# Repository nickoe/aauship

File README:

AAUSHIP
=======
An Autonomous Unmanned Vessel platform

Git repository
--------------
We now have a common git repository we han push to. You can clone it like this
on unix. If you are not familiar with git, I reccomend that you read through
http://gitref.org/, use it as a reference and try to do all of it just to get
familiar with git.

	git clone /afs/ies.auc.dk/www/www.auv.aau.dk/repo/aauship.git

You now have a folder called aauship in the folder you cloned it in.

As you see the repository is directly on AFS, so you have to be authenticated to
 be able to pull and push.

Other stuff that is good to know
https://sites.google.com/site/tjinguytech/charging-how-tos/lipo-terminology

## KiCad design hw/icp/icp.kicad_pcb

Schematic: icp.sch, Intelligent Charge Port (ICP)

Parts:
BZ1: KX1205
C1, C2, C3, C4, C5, C6, C7, C8: 100n
D1: Alarm
D2: ON
D3: Sample
D4: Data
D5: AUX
K1: Tacho0
K2: Tacho1
P1, P2: PX0707/06S
P3, P4: Deans Male
P5, P6: JST-XH
P7: WLD1
P8: I²C
P9: 5V PWR
P10: UART
P11: WLD2
Q1, Q2, Q3, Q4: BC846
R1, R3: 7K5
R2, R4: 2K7
R5, R8, R11, R14, R17, R20: 9K1
R6, R9: 91R
R7, R10: 1K3
R12, R15: 330R
R13, R16: 910R
R18, R21: 560R
R19, R22: 680R
R23, R24, R25, R26, R27, R28, R29, R30: 100R
R31, R32, R34, R36, R37: R
R33, R35, R38, R39: 4K7

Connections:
/atmega2560/ADC0: C2.1, R24.2; also elsewhere on the board
/atmega2560/ADC1: C4.1, R26.2; also elsewhere on the board
/atmega2560/ADC2: C6.1, R28.2; also elsewhere on the board
/atmega2560/ADC3: C8.1, R30.2; also elsewhere on the board
/atmega2560/ADC4: C1.1, R23.2; also elsewhere on the board
/atmega2560/ADC5: C3.1, R25.2; also elsewhere on the board
/atmega2560/ADC6: C5.1, R27.2; also elsewhere on the board
/atmega2560/ADC7: C7.1, R29.2; also elsewhere on the board
/atmega2560/BUZZ: BZ1.2; also elsewhere on the board
/atmega2560/LED0: R37.2; also elsewhere on the board
/atmega2560/LED1: R36.2; also elsewhere on the board
/atmega2560/LED2: R34.2; also elsewhere on the board
/atmega2560/LED3: R32.2; also elsewhere on the board
/atmega2560/LED4: R31.2; also elsewhere on the board
/atmega2560/RXD: P10.5; also elsewhere on the board
/atmega2560/SCL: P8.3, R35.1; also elsewhere on the board
/atmega2560/SDA: P8.2, R33.1; also elsewhere on the board
/atmega2560/TACHO0: K1.2; also elsewhere on the board
/atmega2560/TACHO1: K2.2; also elsewhere on the board
/atmega2560/TXD: P10.4; also elsewhere on the board
/atmega2560/VCC: D1.1 (A), D2.1 (A), D3.1 (A), D4.1 (A), D5.1 (A), K1.3, K2.3, P8.4, P9.3, P9.4, P10.3, R33.2, R35.2, R38.1, R39.1; also elsewhere on the board
/atmega2560/WLD1: Q1.3 (C), Q2.3 (C), R38.2; also elsewhere on the board
/atmega2560/WLD2: Q3.3 (C), Q4.3 (C), R39.2; also elsewhere on the board
GND: BZ1.1, C1.2, C2.2, C3.2, C4.2, C5.2, C6.2, C7.2, C8.2, K1.1, K2.1, P1.1, P2.1, P3.1, P4.1, P5.1, P6.1, P7.1, P8.1, P9.1, P9.2, P10.1, P11.1, Q2.1 (E), Q4.1 (E), R2.2, R4.2, R7.2, R10.2, R13.2, R16.2, R19.2, R22.2; also elsewhere on the board
unnamed: P7.2 (PM), Q1.2 (B)
unnamed: P11.2 (PM), Q3.2 (B)
unnamed: Q3.1 (E), Q4.2 (B)
unnamed: R11.2, R12.1
unnamed: R6.2, R7.1
unnamed: R1.2, R2.1, R23.1
unnamed: R17.2, R18.1
unnamed: R21.2, R22.1, R30.1
unnamed: R15.2, R16.1, R28.1
unnamed: R3.2, R4.1, R24.1
unnamed: R8.2, R9.1, R26.1
unnamed: D5.2 (K), R37.1
unnamed: D4.2 (K), R36.1
unnamed: D3.2 (K), R34.1
unnamed: D2.2 (K), R32.1
unnamed: D1.2 (K), R31.1
unnamed: P2.6, P4.2 (PM)
unnamed: P2.3, P6.3, R8.1
unnamed: P2.4, P6.4, R14.1
unnamed: P2.5, P6.5, R20.1
unnamed: R12.2, R13.1, R27.1
unnamed: R5.2, R6.1, R25.1
unnamed: R18.2, R19.1, R29.1
unnamed: P1.3, P5.3, R5.1
unnamed: P1.4, P5.4, R11.1
unnamed: P1.5, P5.5, R17.1
unnamed: P1.6, P3.2 (PM)
unnamed: P1.2, P5.2, R1.1
unnamed: P2.2, P6.2, R3.1
unnamed: Q1.1 (E), Q2.2 (B)
unnamed: R20.2, R21.1
unnamed: R9.2, R10.1
unnamed: R14.2, R15.1

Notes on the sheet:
Wanted Features - Measure individual cell voltages - Two 4S Li-Po with balancing port - Water Leak Detector (WLD) - Serial and I²C communication - Tachometer for motors
Bank 1
16 kHz lowpass filters
Cell #1
Cell #2
Cell #3
Cell #4
Theese E24 resistor values gives a spread of about 4mV on ADC, which should be sufficient.
Bank 2
Dual tachomoters
Water Leak Detector
Serial
I²C
Mount pull-ups if needed

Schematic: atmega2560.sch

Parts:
C9, C10: 100n
C11, C12: 22p
IC1: ATMEGA168P-20AU; TQFP32
L1: 10µ
X1: 16MHz

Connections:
/atmega2560/ADC0: IC1.23; also elsewhere on the board
/atmega2560/ADC1: IC1.24; also elsewhere on the board
/atmega2560/ADC2: IC1.25; also elsewhere on the board
/atmega2560/ADC3: IC1.26; also elsewhere on the board
/atmega2560/ADC4: IC1.27; also elsewhere on the board
/atmega2560/ADC5: IC1.28; also elsewhere on the board
/atmega2560/ADC6: IC1.19; also elsewhere on the board
/atmega2560/ADC7: IC1.22; also elsewhere on the board
/atmega2560/BUZZ: IC1.15; also elsewhere on the board
/atmega2560/LED0: IC1.14; also elsewhere on the board
/atmega2560/LED1: IC1.10; also elsewhere on the board
/atmega2560/LED2: IC1.16; also elsewhere on the board
/atmega2560/LED3: IC1.17; also elsewhere on the board
/atmega2560/LED4: IC1.11; also elsewhere on the board
/atmega2560/RXD: IC1.31; also elsewhere on the board
/atmega2560/SCL: IC1.9; also elsewhere on the board
/atmega2560/SDA: IC1.2; also elsewhere on the board
/atmega2560/TACHO0: IC1.32; also elsewhere on the board
/atmega2560/TACHO1: IC1.1; also elsewhere on the board
/atmega2560/TXD: IC1.30; also elsewhere on the board
/atmega2560/VCC: C10.2, IC1.20, L1.2; also elsewhere on the board
/atmega2560/WLD1: IC1.12; also elsewhere on the board
/atmega2560/WLD2: IC1.13; also elsewhere on the board
GND: C9.2, C10.1, C11.2, C12.2, IC1.3, IC1.5, IC1.21; also elsewhere on the board
unnamed: C12.1, IC1.7, X1.2
unnamed: C11.1, IC1.8, X1.1
unnamed: C9.1, IC1.18, L1.1

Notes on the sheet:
Place capacitors near pin on chip on PCB layout
Analog supply filter as of some Atmel application note also close to pin
I²C not using hardware, since they are taken by the ADC's so this device does not have to do a lot it can slave easily in software.
The buzzer should be modulated with 50% duty cycle sqyare wave with for example a frequency of 2400 Hz.
As close to chip as possible

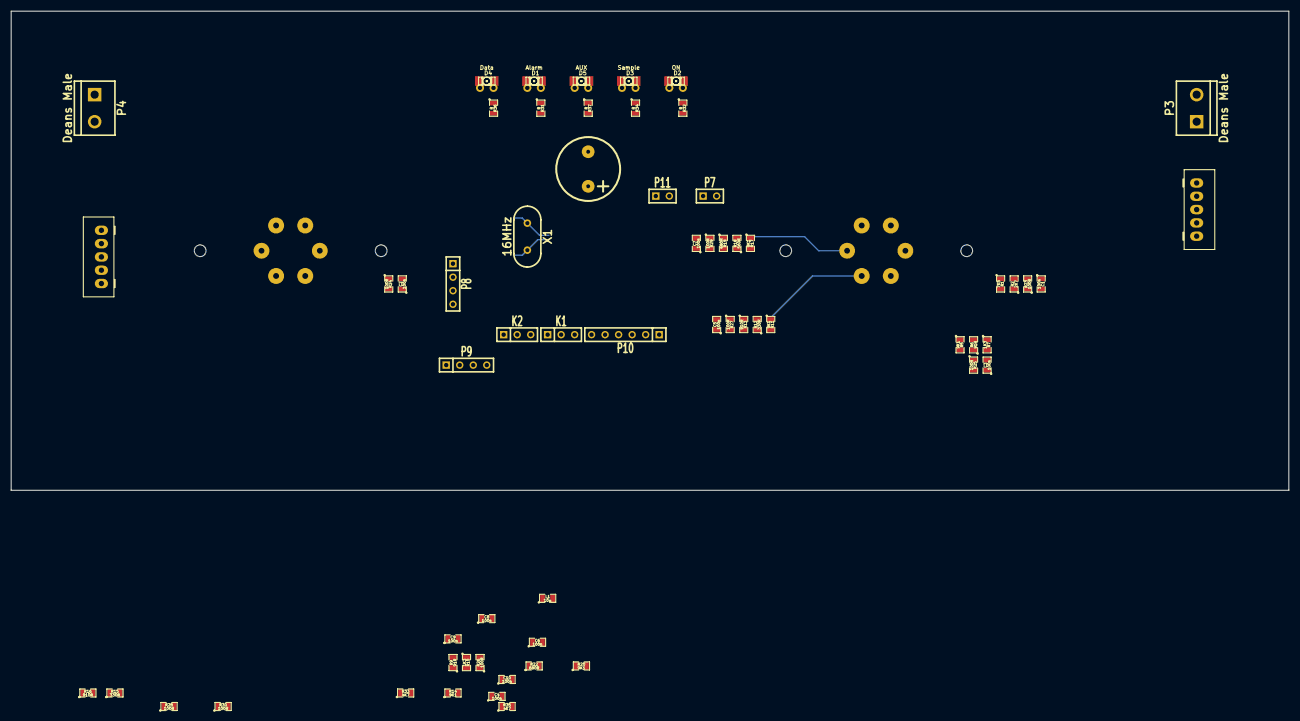
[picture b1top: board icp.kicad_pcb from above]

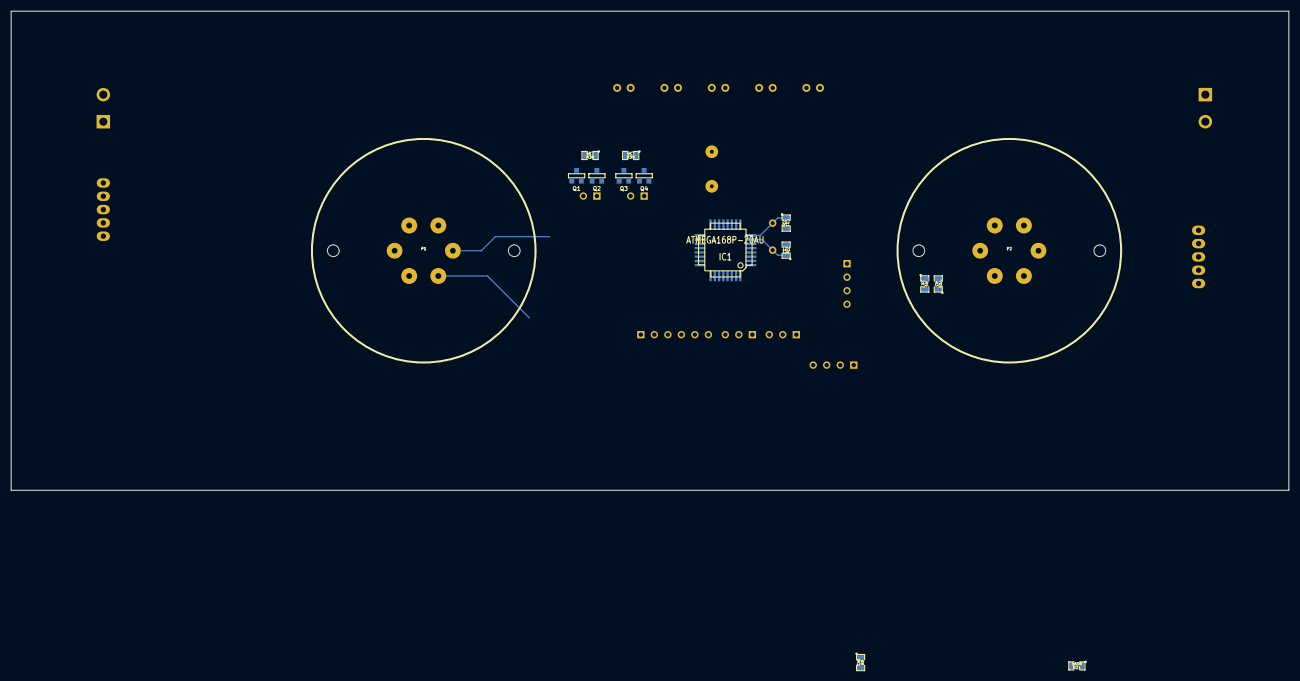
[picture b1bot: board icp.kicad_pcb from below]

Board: 2 copper layers, 240.0 x 90.0 mm, 77 parts (15 on the bottom side), 60 nets.

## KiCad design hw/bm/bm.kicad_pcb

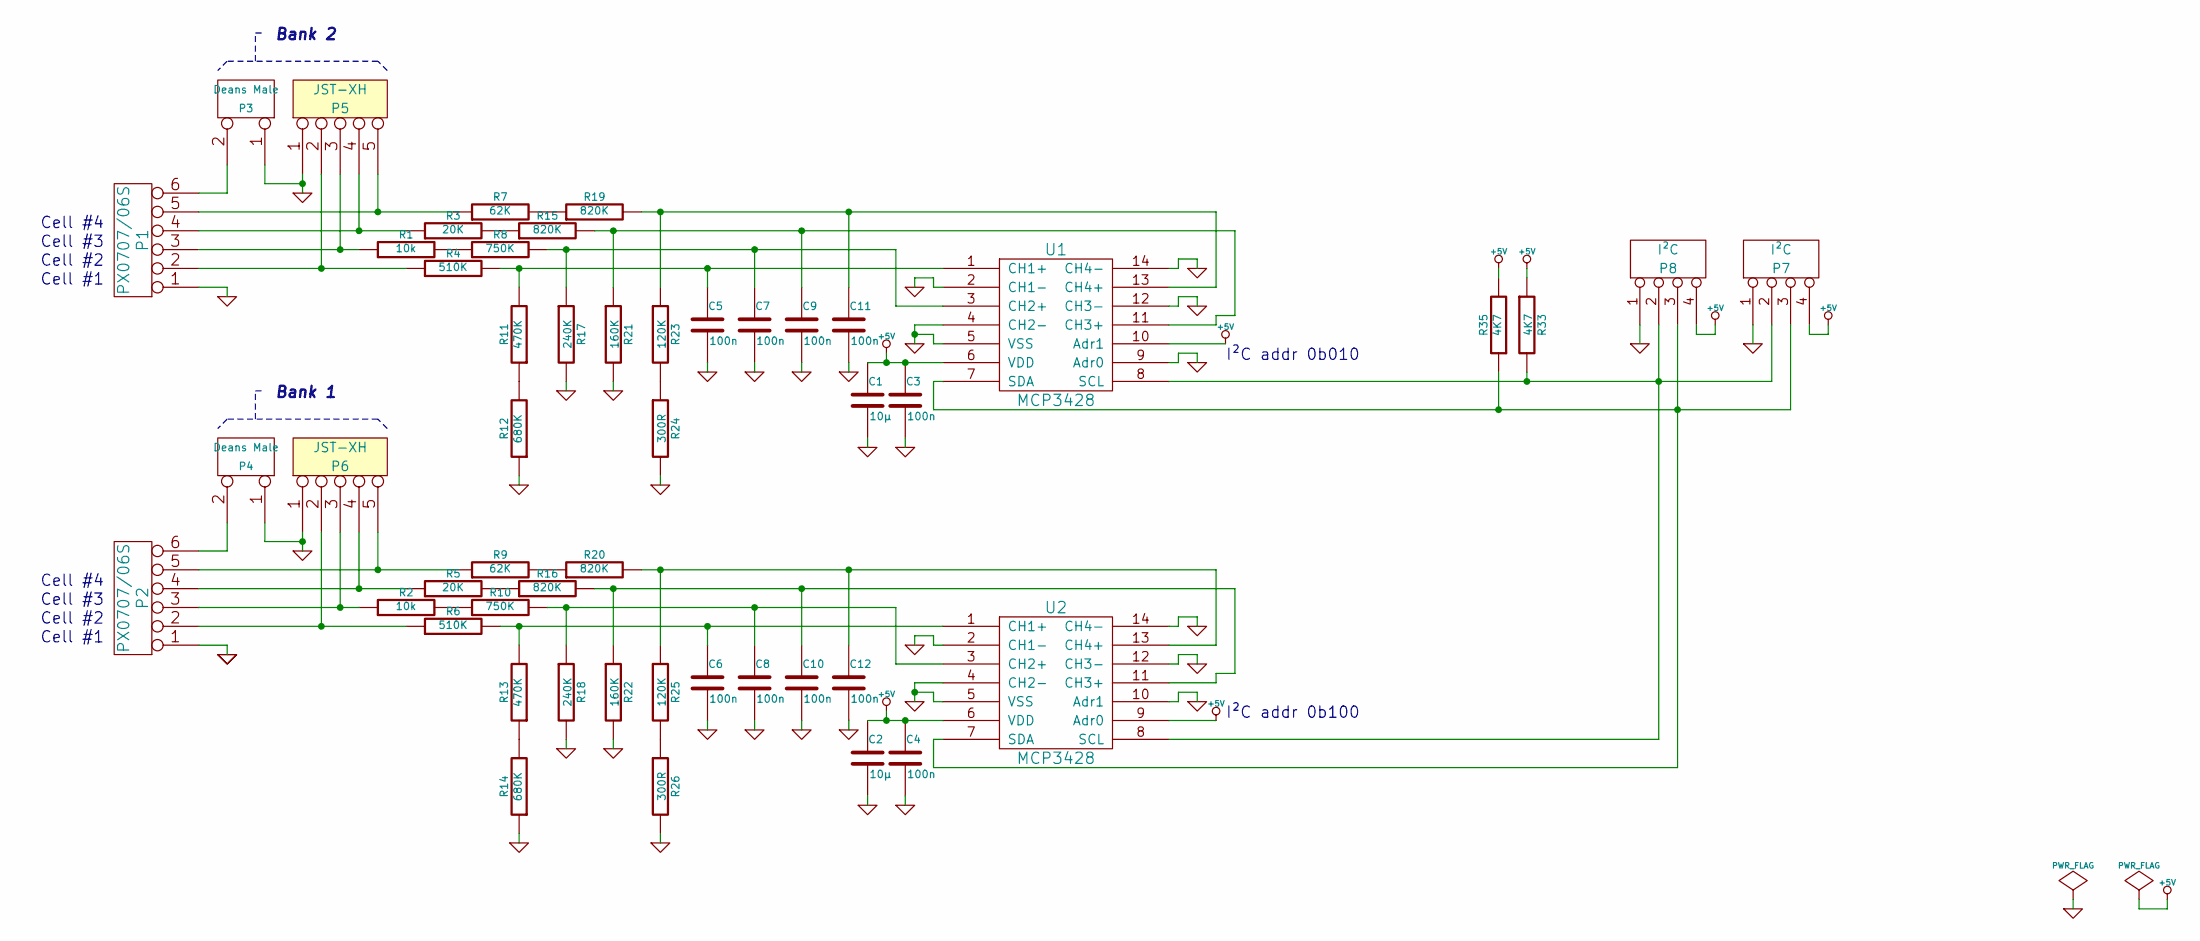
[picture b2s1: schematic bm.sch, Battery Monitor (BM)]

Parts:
C1, C2: 10µ
C3, C4, C5, C6, C7, C8, C9, C10, C11, C12: 100n
P1, P2: PX0707/06S
P3, P4: Deans Male
P5, P6: JST-XH
P7, P8: I²C
R1, R2: 10k
R3, R5: 20K
R4, R6: 510K
R7, R9: 62K
R8, R10: 750K
R11, R13: 470K
R12, R14: 680K
R15, R16, R19, R20: 820K
R17, R18: 240K
R21, R22: 160K
R23, R25: 120K
R24, R26: 300R
R33, R35: 4K7
U1, U2: MCP3428

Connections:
+5V: C1.1, C2.1, C3.1, C4.1, P7.4, P8.4, R33.1, R35.2, U1.6 (VDD), U1.10 (Adr1), U2.6 (VDD), U2.9 (Adr0)
GND: C1.2, C2.2, C3.2, C4.2, C5.2, C6.2, C7.2, C8.2, C9.2, C10.2, C11.2, C12.2, P1.1, P2.1, P3.1, P4.1, P5.1, P6.1, P7.1, P8.1, R12.1, R14.1, R17.2, R18.2, R21.2, R22.2, R24.2, R26.2, U1.2 (CH1-), U1.4 (CH2-), U1.5 (VSS), U1.9 (Adr0), U1.12 (CH3-), U1.14 (CH4-), U2.2 (CH1-), U2.4 (CH2-), U2.5 (VSS), U2.10 (Adr1), U2.12 (CH3-), U2.14 (CH4-)
unnamed: P2.5, P6.5, R9.1
unnamed: P2.4, P6.4, R5.1
unnamed: P2.3, P6.3, R2.1
unnamed: P2.2, P6.2, R6.1
unnamed: C6.1, R6.2, R13.2, U2.1 (CH1+)
unnamed: C12.1, R20.2, R25.1, U2.13 (CH4+)
unnamed: C10.1, R16.2, R22.1, U2.11 (CH3+)
unnamed: C8.1, R10.2, R18.1, U2.3 (CH2+)
unnamed: C11.1, R19.2, R23.1, U1.13 (CH4+)
unnamed: C9.1, R15.2, R21.1, U1.11 (CH3+)
unnamed: C7.1, R8.2, R17.1, U1.3 (CH2+)
unnamed: C5.1, R4.2, R11.2, U1.1 (CH1+)
unnamed: P7.2, P8.2, R33.2, U1.8 (SCL), U2.8 (SCL)
unnamed: P7.3, P8.3, R35.1, U1.7 (SDA), U2.7 (SDA)
unnamed: P1.4, P5.4, R3.1
unnamed: P2.6, P4.2 (PM)
unnamed: P1.5, P5.5, R7.1
unnamed: P1.3, P5.3, R1.1
unnamed: P1.6, P3.2 (PM)
unnamed: P1.2, P5.2, R4.1
unnamed: R7.2, R19.1
unnamed: R3.2, R15.1
unnamed: R1.2, R8.1
unnamed: R11.1, R12.2
unnamed: R25.2, R26.1
unnamed: R9.2, R20.1
unnamed: R5.2, R16.1
unnamed: R23.2, R24.1
unnamed: R2.2, R10.1
unnamed: R13.1, R14.2

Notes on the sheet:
Bank 1
Cell #1
Cell #2
Cell #3
Cell #4
Bank 2
I²C addr 0b010
I²C addr 0b100

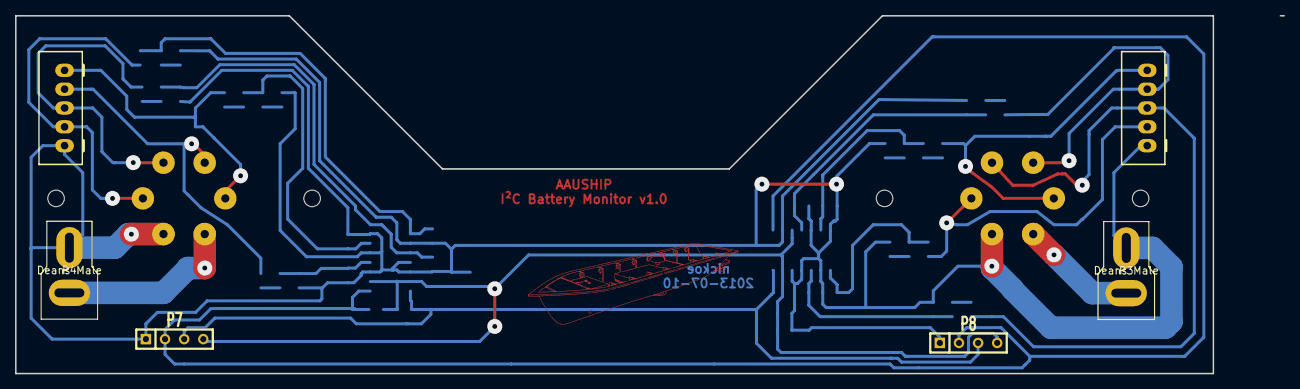
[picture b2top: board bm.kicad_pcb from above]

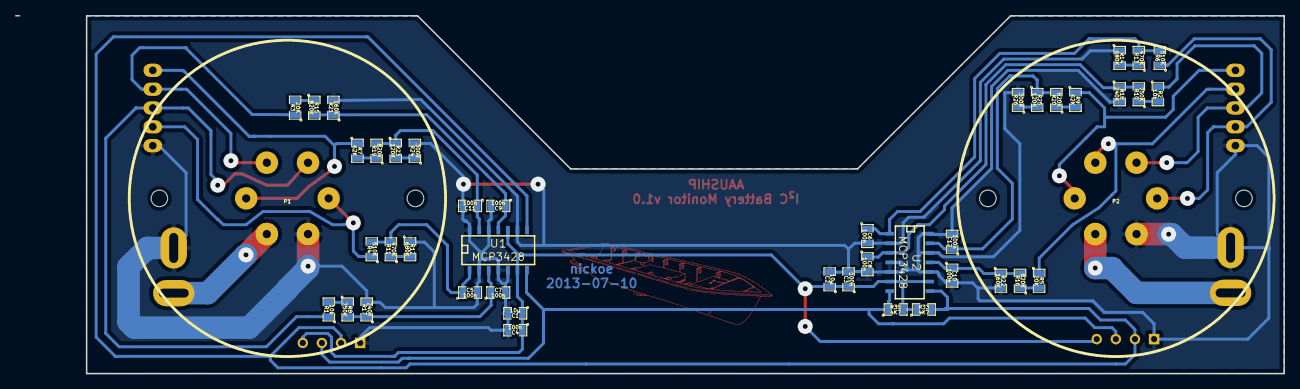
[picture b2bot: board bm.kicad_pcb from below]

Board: 2 copper layers, 168.4 x 47.5 mm, 51 parts (44 on the bottom side), 32 nets.

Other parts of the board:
VAL: aauship

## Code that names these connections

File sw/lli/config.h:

#ifndef CONFIG_H
#define CONFIG_H
/**
 * @file
 * @author Nick Østergaard
 *
 * @section DESCRIPTION
 * This is the configuration file for the LLI interface for AAUSHIP1
 */

#define DEBUG 
#define LOG_ENABLE
#define AUTO_SHUTDOWN_ENABLE
//#define RF_TEST_IDX

extern int awake_flag;
extern uint8_t rmc_idx;

/**
 * Serial rates
 */
// USB connection
#define UART_BAUD_RATE   115200
// APC220/RF7020 radio
#define UART2_BAUD_RATE   38400
// UP-501 GPS
#define UART3_BAUD_RATE    9600


/**
 * Blinkenlights
 */
#define LED1 PL0
#define LED2 PL1
#define LED3 PL2
#define LED4 PL3


/**
 * PWM outputs
 */ 
// OC3 timer
#define DCPWM1 PE4 // OC3B
#define DCPWM2 PE5 // OC3C
#define DCPWM3 PE3 // OC3A
// OC1 timer
#define RCPWM1 PB5 // OC1A
#define RCPWM2 PB6 // OC1B
#define RCPWM3 PB7 // OC1C
// OC4 timer
#define RCPWM4 PH4 // OC4B
#define RCPWM5 PH5 // OC4C

/**
 * Message related stuff
 */
#define MAX_MSG_SIZE 1024  // This should probably be 255 + len + devid + msgid + checksum
#define TX_BUFF_SIZE 350

/* Defines sample rate from the ADIS16405 bt counting interrupt ticks
 * from sample ready pin on device */
//#define ADIS_READY 164 // 10 Hz
#define ADIS_READY 82 // 20Hz
//#define ADIS_READY 42 // 40Hz

/* A hacky timer used to be able to send data in bulk, such the radio
 * can have time to switch from RX to TX and vice versa, to gain
 * better throughput */
#define TX_READY 546 // 3Hz

/* Defines for how many control input packets we can loose without it
 * shutting down */
#define AWAKE_THRESHOLD 3

#endif // CONFIG_H 

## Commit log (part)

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2012-11-20 Clean spi.c for now
2012-11-20 fixed packet parsing and CRC16
2012-11-20 Some changes to the protocol.tex
2012-11-20 Some stuff at the moment, ready for some PROTOCOL sending implementation
2012-11-20 Some minor mods and notes on hw
2012-11-21 Clean CRC a bit
2012-11-21 More CRC cleanup
2012-11-21 Add is_adis16405
2012-11-21 Add crc16.c to makefile
2012-11-21 Now with auto calculatio of length
2012-11-21 Added final postscript and gerbil files to bow thruster folders
2012-11-21 Written some stuff about the protocol
2012-11-21 Update PCB
2012-11-21 Fix warning
2012-11-22 Add hli_send()
2012-11-22 Fix HLI/GRS send fcn
    It need length parameter, C is too lowlevel
2012-11-22 Buildtime variable
2012-11-22 Packethandler minor typo
2012-11-22 Reading stuff ready
2012-11-22 Changes in PacketHandler to use actual serial port
2012-11-22 Transmist and recieves build infor succesfully
2012-11-22 Added moar connections
2012-11-22 Added __GIT_COMMIT__ compiler macro
2012-11-25 Comitting, before i change anything important.
2012-11-25 Burst reading and sending is wokring
2012-11-25 Remove redundant bck file
2012-11-26 Able to testing some measuremnts with a sample time of approx 20 ms
2012-11-26 Push of Matlab file.
2012-11-26 Modify RC PWM signals to the range -500 to 500
2012-11-26 Expand comment
2012-11-27 Changes to protocol and Communication python scripts
2012-11-27 Move GSP section to another page
2012-11-27 Sending GPS sentenses directly
2012-11-28 Subtle changes to LLI hw
2012-11-28 Added Openlogger to LLI board
2012-11-29 Something that seems to work
2012-11-29 Something that still works
2012-11-29 Now 20 Hz
2012-11-29 Something that even still works, experimenting
2012-11-29 Now the logging of IMU and GPS works, partially
    * Still needs verification of sample rate from IMU
    * May still need adjustment of the IMU FIR filter
2012-11-30 Made the IMU sample at 20 Hz
2012-11-30 Changed in the Kalman file and simulation parameters! Subject to change tomorrow.
2012-12-01 Commit!
    With the stuff i've changed.
2012-12-01 Pathplanning-loop fixed
2012-12-01 Remove auto generated files
2012-12-01 Add more ignores!
2012-12-01 Added litterature
2012-12-01 -renamed "bowl" to "bow" in the filenames for the controller -added a "design" chapter to the worksheet -wrote something about the bow thruster
2012-12-01 Pathplaning and embedded simulation finished. Added some lines to the end of the contsimu.m to save the Discrete system matrices (Sys_ABCNF)
2012-12-02 Some final change to the covariance calculations..
    They're still not complete, they are to be tomorrow..
2012-12-03 Remove blank page
2012-12-03 More readability
2012-12-03 Some changes in the package handling stuff
2012-12-04 Added a indicator to which wire for the SD card might not be needed
2012-12-04 Some stuff for the lli that might work
2012-12-04 Note about rightranded systems
2012-12-04 New update to Kalman Filter measurement.
2012-12-04 Remove mat file
2012-12-04 Changed variables so they comply with the Control nomencalture
2012-12-04 Fix annoying formatting
2012-12-04 Added KF to the acronym list.
2012-12-04 Added noise.tex, measurements of the IMU and a figure
2012-12-04 Uploaded GPS and ACC measurements
2012-12-04 Changed Kalman Filter to KF
2012-12-04 Fixed a bug.
2012-12-05 Change somethings in the paper, kalman.m and other
    I added a filter that can be used to simnulate the loss of packages.
    And then i added the title to the Paper..
2012-12-05 Added some text to Kalman.tex about the estimation of delays.
2012-12-05 GPS Measurement Journal
2012-12-05 Fixed references, except the last appendices
2012-12-05 Python Kalman filter, NOT WORKING
2012-12-05 I've reset the path control to the original values, so it works again. Now we have to hammer the kalman filter to outout until it matches the simulator outputs.
2012-12-05 Change to Kalman.
2012-12-06 Some description about LLI electronics
2012-12-06 Commit for Frederik
2012-12-06 Add mutex for LLI, but might be stupid...
2012-12-06 YAAAAAAAAY!!!
2012-12-06 Dummynote
2012-12-06 Changed so the acceleration is now transformed into the body frame.
2012-12-07 Pushed to Attila.
2012-12-07 Non working stuff trying to fix the sampling issue
2012-12-07 Position compensated with KF input, somewhat works.
2012-12-07 added packetloss and fixed crc algorithm
2012-12-07 Changed the HLI so now it works well. Y correction based on Kalman output.
2012-12-07 Manual control working
2012-12-07 A note for the protocol
2012-12-07 Changed before.
2012-12-07 Fix run
2012-12-10 Fix type
2012-12-10 Changes to packetloss, software and introduction
2012-12-10 Stable commit before changes in navigation
2012-12-10 Drag forces documentation
2012-12-10 HLI Core finished. Todo: Relative waypoint adder.
2012-12-10 Move schematics and layout to appendix
2012-12-10 HLI Ready. Should connect it to the Python communicator.
2012-12-10 Adding files so Nisk can change something.
2012-12-10 Added a few words
2012-12-10 Rearrange som section s ans chapters
2012-12-10 CHanged something.
2012-12-10 Read packet loss
2012-12-10 Add fukushima image
2012-12-10 Remove redundant image
2012-12-10 Cite needed
2012-12-10 Tried something else..
2012-12-10 more drag force editing
2012-12-10 Added some text to Kalman.tex.
2012-12-11 Add GPS msg
2012-12-11 Add reduced output for GRS
2012-12-11 Control strategy, some HLI and Pathplanning documentation raw files
2012-12-11 Changes to Kalman.tex and i added soem figures.
2012-12-11 Add more funcitionality
2012-12-11 Changed some files and the kalman.m file so it now outputs the actual error.
2012-12-11 Add desc
2012-12-11 Hej hej.
2012-12-12 Fix rate, and gps logging to SD
2012-12-12 Added some documentation and images to control.tex and software.tex
2012-12-12 Added an Appendix
2012-12-12 More working LLI stuff, still needs diasable call to actuators
2012-12-12 Almost finished with the State Space Model description
2012-12-12 Commit.
2012-12-12 Restore deleted files
2012-12-12 Restore a forgotten file
2012-12-12 Åull.
2012-12-12 Added poster.
2012-12-12 Added some more changes.
2012-12-13 Readd adis lib
2012-12-13 gitignore
2012-12-13 Embedded_test.py added
2012-12-13 Commit of change in Control loop.
2012-12-13 Changed the paper yet again.
2012-12-13 Fix after someone fucked something up..
2012-12-13 Restore images
2012-12-13 Update before i change in master.tex.
2012-12-13 Ready for embedded testing.
2012-12-13 Added awake handle flag, and a define
2012-12-13 Finnally LLI?
2012-12-13 Fix encoding, maybe
2012-12-13 readd stuff
2012-12-13 Did some formatting
2012-12-13 Implemented Kalman filter with communication
2012-12-13 Restore logging parsing stuff
2012-12-14 Changed something in latex_mk.
2012-12-14 Nofilter control commit
2012-12-14 SW Implementation of KF doc added.
2012-12-14 Small change in navigation process.
2012-12-14 Comit before anyone changes it..
    and please stop changing in the kalman.m file - it takes forever to do
    an error correction in the file!
2012-12-14 Commit of model and Kalman.m file - with packet losses.
2012-12-14 Changed Pathplanning
2012-12-14 Faster control
2012-12-14 The coordinate system is configured the right way now
2012-12-14 Made som pdf's for the poster
2012-12-14 Commit of poster.
2012-12-14 Some bigger text
2012-12-14 Ship_nofilter.py for use without the Kalman Filter
2012-12-15 Comitting and syncing.
2012-12-15 Remove temp file
2012-12-15 Cjange.
2012-12-15 Changes to Kalman filter, trying to get it to work
2012-12-15 Added a reference in the litterature file, and added it to the poster.
2012-12-15 Some crap
2012-12-15 Error, test with LOG00206.TXT
2012-12-15 Fix typo
2012-12-16 COmmit of paper and poster so far.
2012-12-16 Correct GPS log
2012-12-16 Changed the paper!
2012-12-16 Added IMU and Control loop introduction documentations.
2012-12-16 Fix makefile
2012-12-16 Edit gitignore
2012-12-16 Updated Paper with Local planner.
2012-12-16 Changes to the packet handling functionality to allow for log parsing
2012-12-16 New commit!
2012-12-16 dfabsd
2012-12-17 Last change to Poster.
2012-12-17 Updated doc & paper, fixed some errors.
2012-12-17 abstract submission!
2012-12-17 Remove more badness
2012-12-17 Commit of Abstract so Nick can work woodoo.
2012-12-17 Edit abstact
2012-12-17 seaborne -> oceanography
2012-12-17 Fit on A4 paper
2012-12-17 Attill's rewrite added
2012-12-17 Something.
2012-12-17 Added the non-used paper files to .gitignore.
2012-12-17 Gitignore.
2012-12-17 Navi figure added
2012-12-17 Fix figures and add more cations to make it more readable
2012-12-17 Changes to the python files to normalize the logging procedure. Added PDF worksheet of the simplex communication
2012-12-17 Added maiden voyage info
2012-12-17 added maiden voyage file
2012-12-17 Push.
2012-12-17 Renders aded
2012-12-17 Oops, pictures again...
2012-12-17 Changed something in the paper.
2012-12-17 Det er fint..
2012-12-17 Added citations to software.tex and introduction.tex, and references to the bib, but they are not working...
2012-12-17 PushPull og alle er glade!
2012-12-17 Compile med fejl.
2012-12-17 some text
2012-12-17 maiden voyage stuff added
2012-12-17 maiden voyage photos`
2012-12-17 forward
2012-12-17 Some more stuff fixed
2012-12-17 Fix more refs
2012-12-17 Some rearrangements
2012-12-17 Re arrangements in protocol
2012-12-17 Change in iaconcf paper.
2012-12-17 Comit before nick changes something.
2012-12-17 and then changed something else.
2012-12-17 Fixed bibliography
2012-12-17 Commit and Sync by me.
    Changes to the paper.
2012-12-17 Addition.
2012-12-17 Added!
2012-12-17 Commit of inserting of image.
2012-12-17 Corpping da pics
2012-12-17 Fixed a paper reference error
2012-12-17 FIXED the coordinate systems in the .py files. Don't change. Added kalmanestimate and motorinput figures for paper
2012-12-17 Removed a todo from Ship design (bow thrust explained)
2012-12-18 some edits
2012-12-18 Fix ref to app
2012-12-18 Rotate figure
2012-12-18 Yet agina - fixing errors.
2012-12-18 asdgasdg
2012-12-18 lli pic added
2012-12-18 Add lli image
2012-12-18 adbadbadfb
2012-12-18 afsgasfgasg
2012-12-18 Finito
2012-12-18 Add precompiled worksheet
2012-12-19 Presentatino.
2012-12-19 new ommit.
2013-01-05 Change
2013-01-05 Changed something and added the master.pdf to the ignor file.
2013-01-05 change server-client to master-slave
2013-01-05 More test C files
2013-01-05 Added RF test index to the databyte[0]
2013-01-05 Addeds ome the.
2013-01-05 More RF test stuff
    Sends a non zero byte in the zeroth byte of the data, which increments by one
    every time it buffers some new GPS or IMU data.
2013-01-05 Changes to Python/Communication to estimate packetloss
2013-01-05 adfgdsfg
2013-01-08 Final changes to comtest and packethandling for probability measurements
2013-01-08 Added figures.
2013-01-11 Control part of the presentation
2013-01-11 Dont change.
2013-01-11 Moved the control part from the presentation to the exam folder. Add \input{control} wherever you want and it'll work. Didn't change anything :)
2013-01-11 Remove RF test
2013-01-11 First iteration of my slides
2013-01-11 some files i forgot
2013-01-11 COmit
2013-01-11 controlloop
2013-01-11 Fix the unicode error in latex
2013-01-11 Kom igang
2013-01-11 and photos
2013-01-11 afadf
2013-01-11 vb,hgg,gi
2013-01-11 Comitted and added a picture.
2013-02-21 new paper
2013-02-27 changes.
2013-02-27 Some updates
2013-07-01 Some ICP stuff
2013-07-03 Add a link
2013-07-04 Update schematic for ICP
2013-07-08 More ICP
2013-07-10 Modify ignore file
2013-07-11 Attribution to Pascal Stang
2013-07-11 Comments in config.h
2013-07-11 Remove whitespace
2013-07-12 Add logger script for new voyage
2013-07-12 Logger ready possibly, test in rpi
